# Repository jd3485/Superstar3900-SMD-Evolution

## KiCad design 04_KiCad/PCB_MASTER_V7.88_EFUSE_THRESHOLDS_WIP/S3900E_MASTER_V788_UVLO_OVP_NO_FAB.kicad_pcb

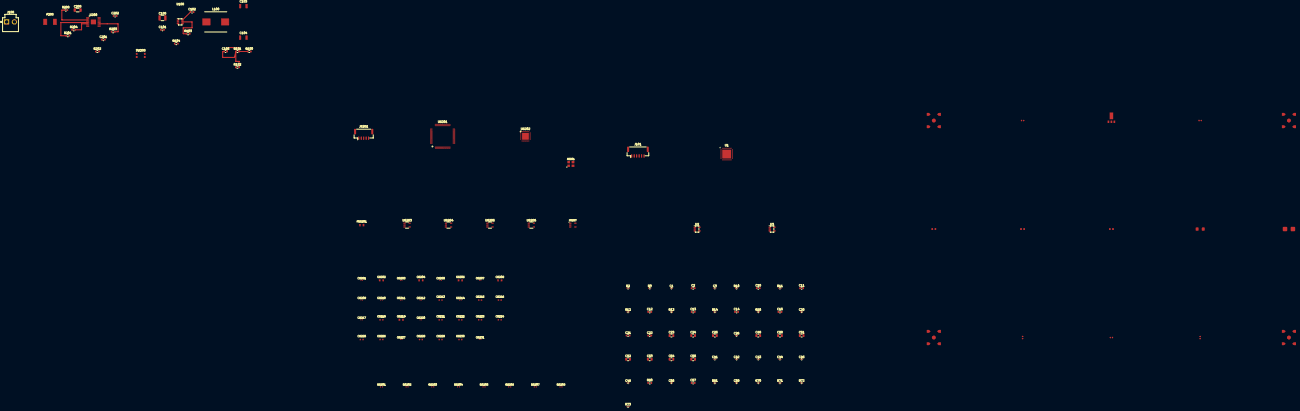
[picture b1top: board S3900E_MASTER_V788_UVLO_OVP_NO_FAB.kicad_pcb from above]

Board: 2 copper layers, 139 parts (0 on the bottom side), 83 nets.

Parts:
C1: 220p C0G; C_0402_1005Metric
C2: 120n X7R; C_0603_1608Metric
C3: 2n2 C0G; C_0402_1005Metric
C10, C11, C12, C13, C14, C15: 1u X7R; C_0603_1608Metric
C20: 100n; C_0402_1005Metric
C21: 1u; C_0603_1608Metric
C22: 470n; C_0603_1608Metric
C23, C24, C25: 10u; C_0805_2012Metric
C26: 10n; C_0402_1005Metric
C40: 10u X7R; C_0805_2012Metric
C41, C42, C43, C44, C45, C46, C56: 100n 10V X7R; C_0402_1005Metric
C50, C53: 2u2 10V X7R; C_0805_2012Metric
C51, C54: 4u7 10V X7R; C_0805_2012Metric
C52, C55: 10u 10V X7R; C_0805_2012Metric
C57: 1u 10V X7R; C_0603_1608Metric
C58: 100n X7R; C_0402_1005Metric
C100: 10uF 35V X7R; C_1210_3225Metric
C101: 100nF 50V X7R; C_0603_1608Metric
C102: 100nF 25V X7R; C_0603_1608Metric
C103, C104: 22uF 25V X7R; TDK_CGA6_1210_AECQ200_C103_C104_VENDOR_LAND_HOLD
C105: 75pF 50V C0G; C_0603_1608Metric
C200: 100nF 100V X7R; C_1206_3216Metric
C201: 22nF 50V X7R; C_0603_1608Metric
C202: 1uF 35V X7R; C_0603_1608Metric
C6201, C6203, C6205, C6207, C6209, C6210, C6211, C6212, C6214, C6217, C6220, C6227, C6231: 100nF; MURATA_GRM15_0402_REFLOW_REVIEW
C6202, C6204, C6206, C6208, C6219: 10uF; TDK_C2012_0805_10UF_REFLOW_REVIEW
C6213, C6215, C6216, C6218, C6221, C6222, C6223, C6224, C6225, C6226, C6229: 1uF; TDK_C1608_0603_1UF_REFLOW_REVIEW
C6228: 4.7nF; TDK_C1608_0603_C0G_REFLOW_REVIEW
C6230: 10nF; TDK_C1608_0603_C0G_REFLOW_REVIEW
C9101, C9102: 100nF; C_0402
C9103: 68pF; C_0603
C9104: 1.2nF; C_0603
C9105: 1uF; C_1206
F200: 1.5A 045101.5MRL CANDIDATO; LF451_045101_5MRL_VENDOR_CANDIDATE
FB6201: 600R@100MHz_TDK_2A_REVIEW; TDK_MPZ2012_0805_POWER_BEAD_REFLOW_REVIEW
J100: INGRESSO_AUX_13V8_DRAFT; JST_VH_B2P-VH_1x02_P3.96mm_Vertical
J101: HOST_SPI_3V3_DRAFT; JST_GH_BM06B-GHS-TBT_1x06-1MP_P1.25mm_Vertical
J6201: BM05B-GHS-TBT(LF)(SN); JST_GH_BM05B-GHS-TBT_1x05-1MP_P1.25mm_Vertical
J9101: SMA LNA IN; CONSMA002_SMD_SHAPED_REVIEW
J9102: SMA LNA OUT; CONSMA002_SMD_SHAPED_REVIEW
J9103: SMA PAD IN; CONSMA002_SMD_SHAPED_REVIEW
J9104: SMA PAD OUT; CONSMA002_SMD_SHAPED_REVIEW
J9105: 5V BENCH; 2_wire_solder_pads
L100: 15uH SRP1038A-150M; SRP1038A_150M_BOURNS_VENDOR_CANDIDATE
L9101: 470nH; L_0603
R2: 620R; R_0402_1005Metric
R3: 22R; R_0402_1005Metric
R10, R11, R12, R13, R14, R15: 0R; R_0402_1005Metric
R60: 10k 1pct; R_0603_1608Metric
R61: 33R 1pct; R_0402_1005Metric
R70, R71, R72, R73: 10k 1pct; R_0402_1005Metric
R100: 49R9 1%; R_0603_1608Metric
R101: 100k 1%; R_0603_1608Metric
R102: 13k3 1%; R_0603_1608Metric
R103: 510k 5%; R_0603_1608Metric
R104: 105k 1%; R_0603_1608Metric
R200: 365k 1%; R_0603_1608Metric
R201: 16k2 1%; R_0603_1608Metric
R202: 30k1 1%; R_0603_1608Metric
R203: 8k2 1%; R_0603_1608Metric
R204: 402k 1% MODE_LATCHOFF_CANDIDATE; R_0603_1608Metric
R6201: 47k; YAGEO_RC0402_REFLOW_VENDOR_CANDIDATE
R6202, R6203, R6204, R6206: 4.7k; YAGEO_RC0402_REFLOW_VENDOR_CANDIDATE
R6205: 33R; YAGEO_RC0402_REFLOW_VENDOR_CANDIDATE
R6207, R6208: 1k; YAGEO_RC0402_REFLOW_VENDOR_CANDIDATE
R9201, R9202: 150R; R_0402_SHUNT_PERPENDICULAR
R9203: 37.4R; R_0402
SW200: KMR223NG ULC LFG (CANDIDATE); CK_KMR223NG_ULC_LFG_4PAD_VENDOR_LAND_REVIEW
U1: LMX2572RHA; LMX2572_RHA0040H_VENDOR_CANDIDATE
U2, U3: TPS7A2033PDBVR; SOT-23-5
U100: TPS54202DDCR; SOT-23-6
U200: TPS26600PWPT; TPS26600_PWP0016H_EXAMPLE_LAND_REVIEW
U6201: STM32G474RET6 (DRAFT); STM32G474RE_LQFP64_ST_DS12288_CANDIDATE
U6202: TLV320AIC3204 (DRAFT); TLV320AIC3204_RHB0032E_VENDOR_CANDIDATE
U6203, U6204, U6205, U6206: TPS7A2033PDBVR; TPS7A20_DBV0005A_VENDOR_CANDIDATE
U6207: TPS3840PL30DBVR; TI_DBV0005A_5PAD_REFLOW_REVIEW
U9101: ADL5535; ADL5535_SOT89_PASTE_REVIEW
X6201: SiT8008AI-22-33E-12.288000; SiT8008AI_3225_VENDOR_CANDIDATE

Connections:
/AUX_POWER_existing_V1_5_UNQUALIFIED/01 PROTEZIONE AUX/BUCK_VIN_PROTECTED: C100.2, C101.2, C202.2, R103.2, U100.3, U200.15, U200.16
/AUX_POWER_existing_V1_5_UNQUALIFIED/01 PROTEZIONE AUX/DV_DT_NODE: C201.2, U200.12
/AUX_POWER_existing_V1_5_UNQUALIFIED/01 PROTEZIONE AUX/EFUSE_MODE: R204.2, U200.6
/AUX_POWER_existing_V1_5_UNQUALIFIED/01 PROTEZIONE AUX/EFUSE_RTN: C201.1, R202.1, R203.1, R204.1, U200.8, U200.17
/AUX_POWER_existing_V1_5_UNQUALIFIED/01 PROTEZIONE AUX/EFUSE_SHDN_RESET_N: SW200.1, SW200.4, U200.7
/AUX_POWER_existing_V1_5_UNQUALIFIED/01 PROTEZIONE AUX/EFUSE_VIN: C200.2, F200.2, R200.2, U200.1, U200.2
/AUX_POWER_existing_V1_5_UNQUALIFIED/01 PROTEZIONE AUX/ILIM_NODE: R203.2, U200.11
/AUX_POWER_existing_V1_5_UNQUALIFIED/01 PROTEZIONE AUX/OVP_NODE: R201.1, R202.2, U200.5
/AUX_POWER_existing_V1_5_UNQUALIFIED/01 PROTEZIONE AUX/UVLO_NODE: R200.1, R201.2, U200.3
/AUX_POWER_existing_V1_5_UNQUALIFIED/02 BUCK 5V/5V_RF_PREREGULATED: C50.2, C53.2, C103.2, C104.2, L100.2, R100.2, U2.1, U2.3, U3.1, U3.3
/AUX_POWER_existing_V1_5_UNQUALIFIED/02 BUCK 5V/BUCK_BOOT: C102.1, U100.6
/AUX_POWER_existing_V1_5_UNQUALIFIED/02 BUCK 5V/BUCK_DIV_TOP: C105.2, R100.1, R101.2
/AUX_POWER_existing_V1_5_UNQUALIFIED/02 BUCK 5V/BUCK_EN: R103.1, R104.2, U100.5
/AUX_POWER_existing_V1_5_UNQUALIFIED/02 BUCK 5V/BUCK_FB: C105.1, R101.1, R102.2, U100.4
/AUX_POWER_existing_V1_5_UNQUALIFIED/02 BUCK 5V/BUCK_SW: C102.2, L100.1, U100.2
/AUX_POWER_existing_V1_5_UNQUALIFIED/03 PLL + LDO + TCXO/3V3_PLL_INPUT_FROM_LDO: C40.2, C51.2, C52.2, R10.2, R11.2, R12.2, R13.2, R14.2, R15.2, U2.5
/AUX_POWER_existing_V1_5_UNQUALIFIED/03 PLL + LDO + TCXO/3V3_REF_LDO: C54.2, C55.2, C56.2, C57.2, R60.2, U3.5
/AUX_POWER_existing_V1_5_UNQUALIFIED/03 PLL + LDO + TCXO/PLL_CPOUT: C1.2, R2.1, R3.1, U1.12
/AUX_POWER_existing_V1_5_UNQUALIFIED/03 PLL + LDO + TCXO/PLL_OSCINP_AC: C58.2, U1.8
/AUX_POWER_existing_V1_5_UNQUALIFIED/03 PLL + LDO + TCXO/PLL_R2_C2: C2.2, R2.2
/AUX_POWER_existing_V1_5_UNQUALIFIED/03 PLL + LDO + TCXO/PLL_RAMPCLK_PENDING: R72.1, U1.30
/AUX_POWER_existing_V1_5_UNQUALIFIED/03 PLL + LDO + TCXO/PLL_RAMPDIR_PENDING: R73.1, U1.32
/AUX_POWER_existing_V1_5_UNQUALIFIED/03 PLL + LDO + TCXO/PLL_SYNC_PENDING: R70.1, U1.5
/AUX_POWER_existing_V1_5_UNQUALIFIED/03 PLL + LDO + TCXO/PLL_SYSREFREQ_PENDING: R71.1, U1.28
/AUX_POWER_existing_V1_5_UNQUALIFIED/03 PLL + LDO + TCXO/PLL_VBIASVARAC: C24.2, U1.33
/AUX_POWER_existing_V1_5_UNQUALIFIED/03 PLL + LDO + TCXO/PLL_VBIASVCO: C20.2, U1.3
/AUX_POWER_existing_V1_5_UNQUALIFIED/03 PLL + LDO + TCXO/PLL_VBIASVCO2: C22.2, U1.27
/AUX_POWER_existing_V1_5_UNQUALIFIED/03 PLL + LDO + TCXO/PLL_VCCBUF: C13.2, C44.2, R13.1, U1.21
/AUX_POWER_existing_V1_5_UNQUALIFIED/03 PLL + LDO + TCXO/PLL_VCCCP: C11.2, C42.2, R11.1, U1.11
/AUX_POWER_existing_V1_5_UNQUALIFIED/03 PLL + LDO + TCXO/PLL_VCCDIG: C10.2, C41.2, R10.1, U1.7
/AUX_POWER_existing_V1_5_UNQUALIFIED/03 PLL + LDO + TCXO/PLL_VCCMASH: C12.2, C43.2, R12.1, U1.15
/AUX_POWER_existing_V1_5_UNQUALIFIED/03 PLL + LDO + TCXO/PLL_VCCVCO: C15.2, C46.2, R15.1, U1.37
/AUX_POWER_existing_V1_5_UNQUALIFIED/03 PLL + LDO + TCXO/PLL_VCCVCO2: C14.2, C45.2, R14.1, U1.26
/AUX_POWER_existing_V1_5_UNQUALIFIED/03 PLL + LDO + TCXO/PLL_VREFVCO: C25.2, U1.36
/AUX_POWER_existing_V1_5_UNQUALIFIED/03 PLL + LDO + TCXO/PLL_VREFVCO2: C23.2, U1.29
/AUX_POWER_existing_V1_5_UNQUALIFIED/03 PLL + LDO + TCXO/PLL_VREGIN: C21.2, U1.10
/AUX_POWER_existing_V1_5_UNQUALIFIED/03 PLL + LDO + TCXO/PLL_VREGVCO: C26.2, U1.38
/AUX_POWER_existing_V1_5_UNQUALIFIED/03 PLL + LDO + TCXO/PLL_VTUNE: C3.2, R3.2, U1.35
/AUX_POWER_existing_V1_5_UNQUALIFIED/03 PLL + LDO + TCXO/TCXO_CMOS_DAMPED: C58.1, R61.2
/AUX_POWER_existing_V1_5_UNQUALIFIED/GND_MAIN: C1.1, C2.1, C3.1, C10.1, C11.1, C12.1, C13.1, C14.1, C15.1, C20.1, C21.1, C22.1, C23.1, C24.1, C25.1, C26.1, C40.1, C41.1, C42.1, C43.1, C44.1, C45.1, C46.1, C50.1, C51.1, C52.1, C53.1, C54.1, C55.1, C56.1, C57.1, C100.1, C101.1, C103.1, C104.1, C200.1, C202.1, J100.2, J101.6, R70.2, R71.2, R72.2, R73.2, R102.1, R104.1, SW200.2, SW200.3, U1.2, U1.4, U1.6, U1.13, U1.14, U1.25, U1.31, U1.34, U1.39, U1.40, U1.41, U2.2, U3.2, U100.1, U200.9
/AUX_POWER_existing_V1_5_UNQUALIFIED/PLL_CE: J101.4, U1.1
/AUX_POWER_existing_V1_5_UNQUALIFIED/PLL_CSB: J101.3, U1.24
/AUX_POWER_existing_V1_5_UNQUALIFIED/PLL_MUXOUT: J101.5, U1.20
/AUX_POWER_existing_V1_5_UNQUALIFIED/PLL_SCK: J101.1, U1.16
/AUX_POWER_existing_V1_5_UNQUALIFIED/PLL_SDI: J101.2, U1.17
/AUX_POWER_existing_V1_5_UNQUALIFIED/PWR_13V8_AUX_RAW: F200.1, J100.1
/MCU_CODEC_AFE_existing_V2_1_UNQUALIFIED/3V3_ANA_MCU: C6214.1, U6201.28, U6201.29
/MCU_CODEC_AFE_existing_V2_1_UNQUALIFIED/3V3_AUDIO_CLK: C6216.1, C6217.1, C6218.1, R6204.1, U6203.5, X6201.4
/MCU_CODEC_AFE_existing_V2_1_UNQUALIFIED/3V3_CODEC_IO: C6201.1, C6224.1, C6231.1, R6202.2, R6203.2, R6206.1, U6202.6, U6205.5, U6207.2
/MCU_CODEC_AFE_existing_V2_1_UNQUALIFIED/3V3_CODEC_LDOIN: C6207.1, C6208.1, C6226.1, U6202.26, U6206.5
/MCU_CODEC_AFE_existing_V2_1_UNQUALIFIED/3V3_MCU: C6209.1, C6210.1, C6211.1, C6212.1, C6213.1, C6222.1, J6201.1, U6201.1, U6201.16, U6201.32, U6201.48, U6201.64, U6204.5
/MCU_CODEC_AFE_existing_V2_1_UNQUALIFIED/5V_DIGITAL_FILTERED: C6215.1, C6219.1, C6220.1, C6221.1, C6223.1, C6225.1, FB6201.2, U6203.1, U6203.3, U6204.1, U6204.3, U6205.1, U6205.3, U6206.1
/MCU_CODEC_AFE_existing_V2_1_UNQUALIFIED/AUDIO_BCLK: U6201.30, U6202.2
/MCU_CODEC_AFE_existing_V2_1_UNQUALIFIED/AUDIO_I2S_RX: U6201.58, U6202.5
/MCU_CODEC_AFE_existing_V2_1_UNQUALIFIED/AUDIO_I2S_TX: U6201.9, U6202.4
/MCU_CODEC_AFE_existing_V2_1_UNQUALIFIED/AUDIO_MCLK_12M288: R6205.2, U6202.1
/MCU_CODEC_AFE_existing_V2_1_UNQUALIFIED/AUDIO_WCLK: U6201.43, U6202.3
/MCU_CODEC_AFE_existing_V2_1_UNQUALIFIED/CODEC_AVDD_LDO_OUT: C6203.1, C6204.1, U6202.24
/MCU_CODEC_AFE_existing_V2_1_UNQUALIFIED/CODEC_DVDD_LDO_OUT: C6205.1, C6206.1, U6202.29
/MCU_CODEC_AFE_existing_V2_1_UNQUALIFIED/CODEC_I2C_SCL: R6202.1, U6201.59, U6202.9
/MCU_CODEC_AFE_existing_V2_1_UNQUALIFIED/CODEC_I2C_SDA: R6203.1, U6201.60, U6202.10
/MCU_CODEC_AFE_existing_V2_1_UNQUALIFIED/CODEC_LDOIN_EN_SUPERVISED: U6206.3, U6207.1
/MCU_CODEC_AFE_existing_V2_1_UNQUALIFIED/CODEC_LDO_SELECT: R6206.2, U6202.30
/MCU_CODEC_AFE_existing_V2_1_UNQUALIFIED/CODEC_REF: C6202.1, U6202.18
/MCU_CODEC_AFE_existing_V2_1_UNQUALIFIED/CODEC_RESET_N: R6201.1, U6201.10, U6202.31
/MCU_CODEC_AFE_existing_V2_1_UNQUALIFIED/FM_AC_COUPLED: C6229.2, R6208.1
/MCU_CODEC_AFE_existing_V2_1_UNQUALIFIED/FM_CODEC_IN: C6230.1, R6208.2, U6202.16
/MCU_CODEC_AFE_existing_V2_1_UNQUALIFIED/GND: C6201.2, C6202.2, C6203.2, C6204.2, C6205.2, C6206.2, C6207.2, C6208.2, C6209.2, C6210.2, C6211.2, C6212.2, C6213.2, C6214.2, C6215.2, C6216.2, C6217.2, C6218.2, C6219.2, C6220.2, C6221.2, C6222.2, C6223.2, C6224.2, C6225.2, C6226.2, C6228.2, C6230.2, C6231.2, J6201.5, R6201.2, U6201.15, U6201.27, U6201.31, U6201.47, U6201.63, U6202.7, U6202.12, U6202.17, U6202.28, U6202.33, U6203.2, U6204.2, U6205.2, U6206.2, U6207.3, X6201.2
/MCU_CODEC_AFE_existing_V2_1_UNQUALIFIED/MCU_NRST: J6201.4, U6201.7
/MCU_CODEC_AFE_existing_V2_1_UNQUALIFIED/MCU_SWCLK: J6201.3, U6201.50
/MCU_CODEC_AFE_existing_V2_1_UNQUALIFIED/MCU_SWDIO: J6201.2, U6201.49
/MCU_CODEC_AFE_existing_V2_1_UNQUALIFIED/MIC_AC_COUPLED: C6227.2, R6207.1
/MCU_CODEC_AFE_existing_V2_1_UNQUALIFIED/MIC_CODEC_IN: C6228.1, R6207.2, U6202.13
/MCU_CODEC_AFE_existing_V2_1_UNQUALIFIED/XO_MCLK_RAW: R6205.1, X6201.3
/MCU_CODEC_AFE_existing_V2_1_UNQUALIFIED/XO_OE: R6204.2, X6201.1
/RX_50OHM_coupon_existing_V5_2_UNQUALIFIED/+5V_BENCH: C9103.1, C9104.1, C9105.1, J9105.1, L9101.1
/RX_50OHM_coupon_existing_V5_2_UNQUALIFIED/GND_RF: C9103.2, C9104.2, C9105.2, J9101.2, J9102.2, J9103.2, J9104.2, J9105.2, R9201.2, R9202.2, U9101.2
/RX_50OHM_coupon_existing_V5_2_UNQUALIFIED/RF_ATTEN_IN: J9103.1, R9201.1, R9203.1
/RX_50OHM_coupon_existing_V5_2_UNQUALIFIED/RF_ATTEN_OUT: J9104.1, R9202.1, R9203.2
/RX_50OHM_coupon_existing_V5_2_UNQUALIFIED/RF_BIAS_OUT: C9102.1, L9101.2, U9101.3
/RX_50OHM_coupon_existing_V5_2_UNQUALIFIED/RF_LNA_IC_IN: C9101.2, U9101.1
/RX_50OHM_coupon_existing_V5_2_UNQUALIFIED/RF_LNA_INPUT: C9101.1, J9101.1
/RX_50OHM_coupon_existing_V5_2_UNQUALIFIED/RF_LNA_OUT: C9102.2, J9102.1
